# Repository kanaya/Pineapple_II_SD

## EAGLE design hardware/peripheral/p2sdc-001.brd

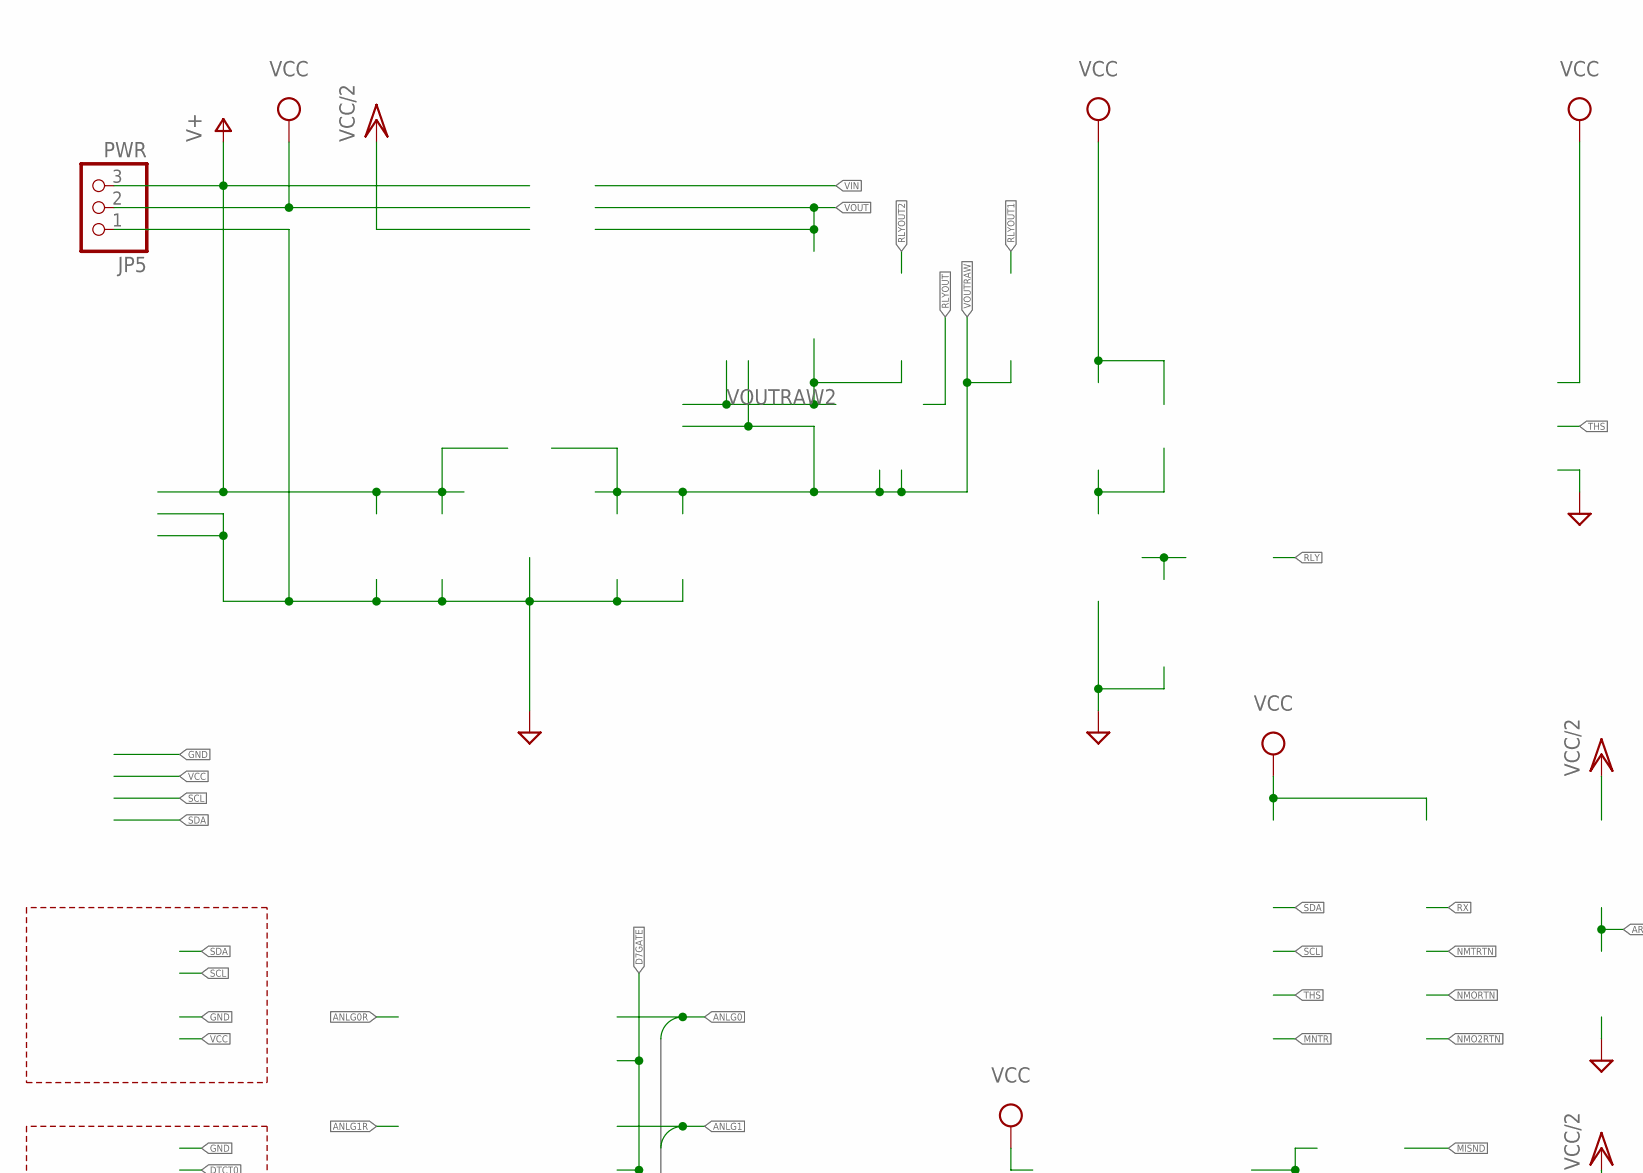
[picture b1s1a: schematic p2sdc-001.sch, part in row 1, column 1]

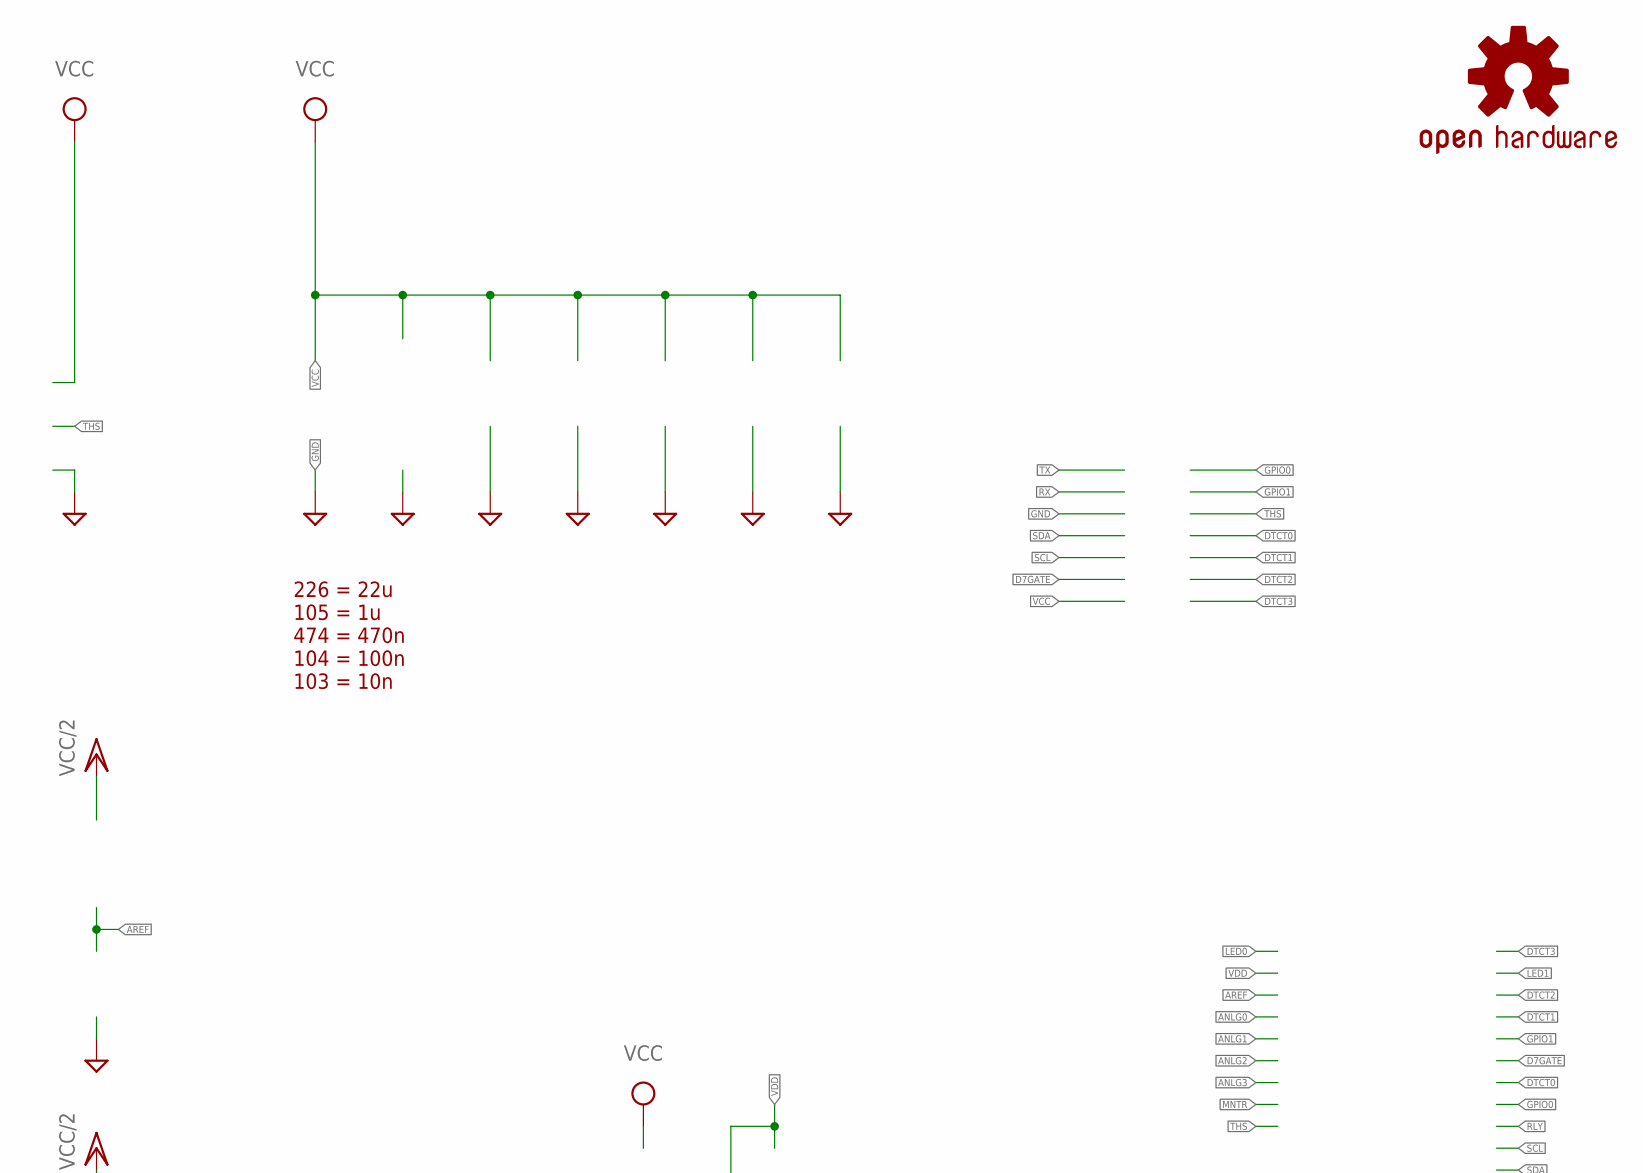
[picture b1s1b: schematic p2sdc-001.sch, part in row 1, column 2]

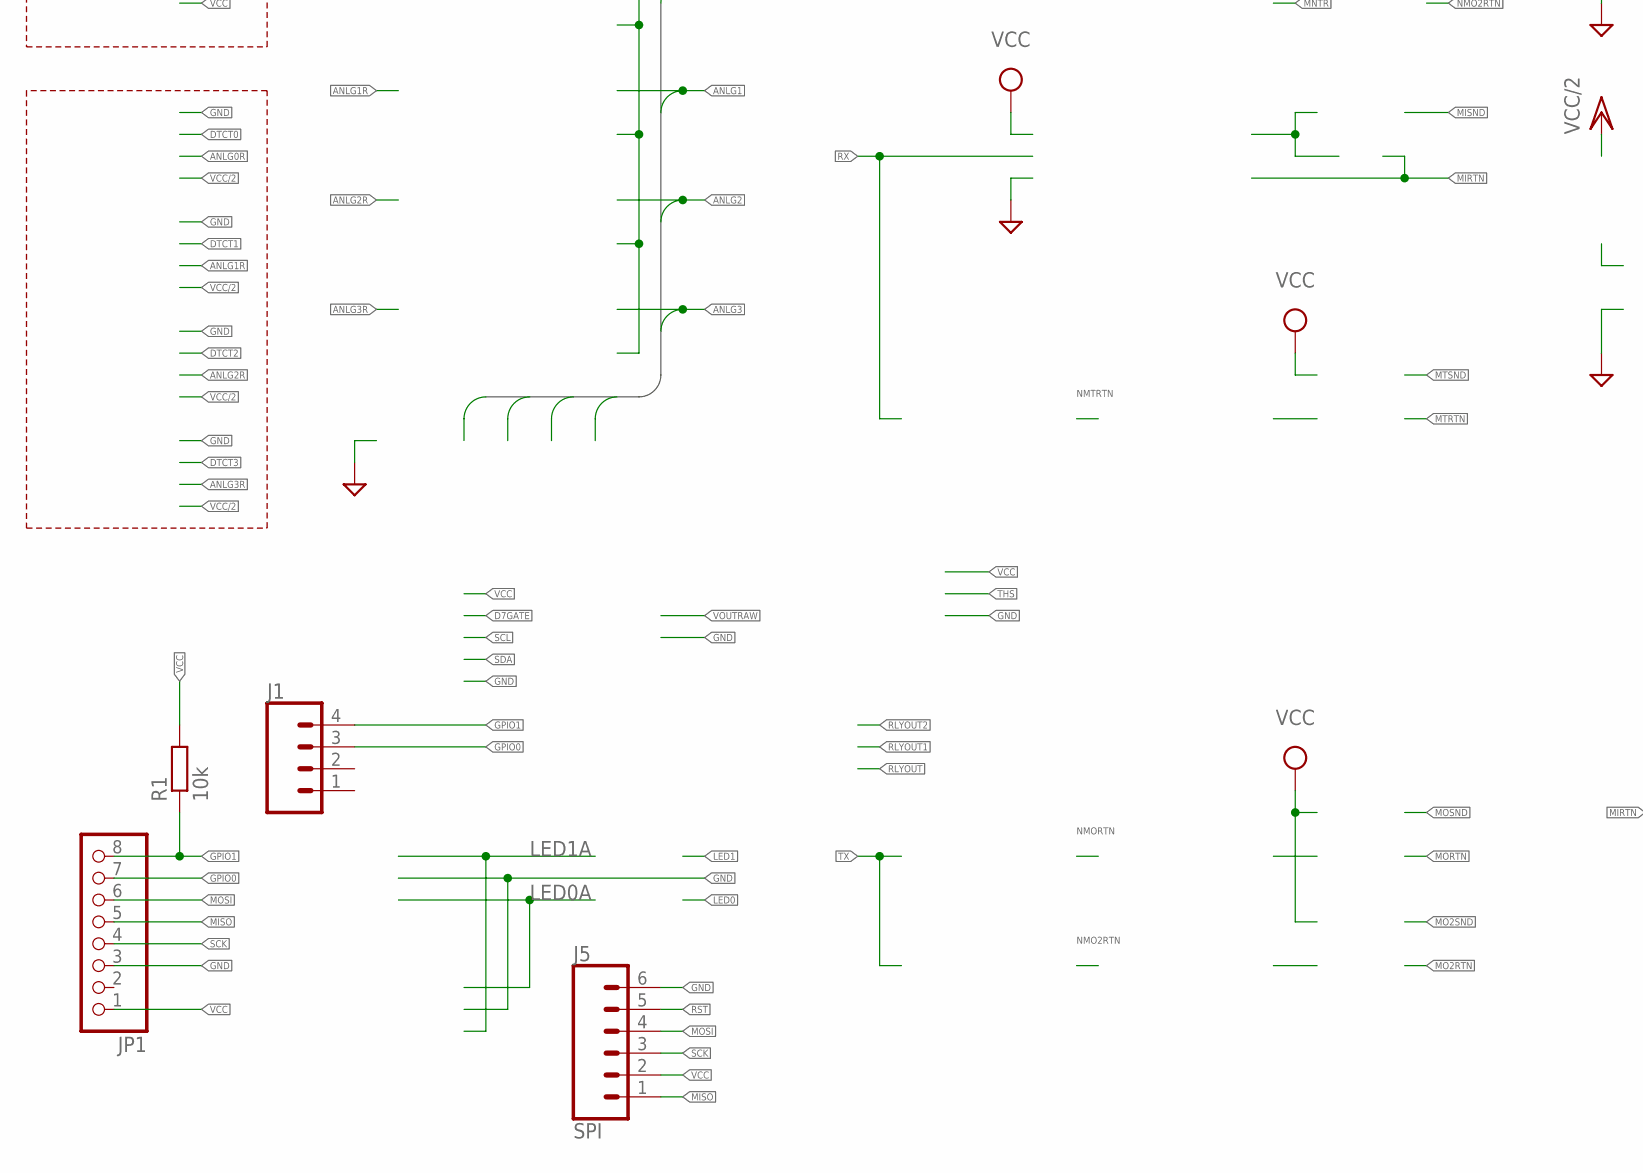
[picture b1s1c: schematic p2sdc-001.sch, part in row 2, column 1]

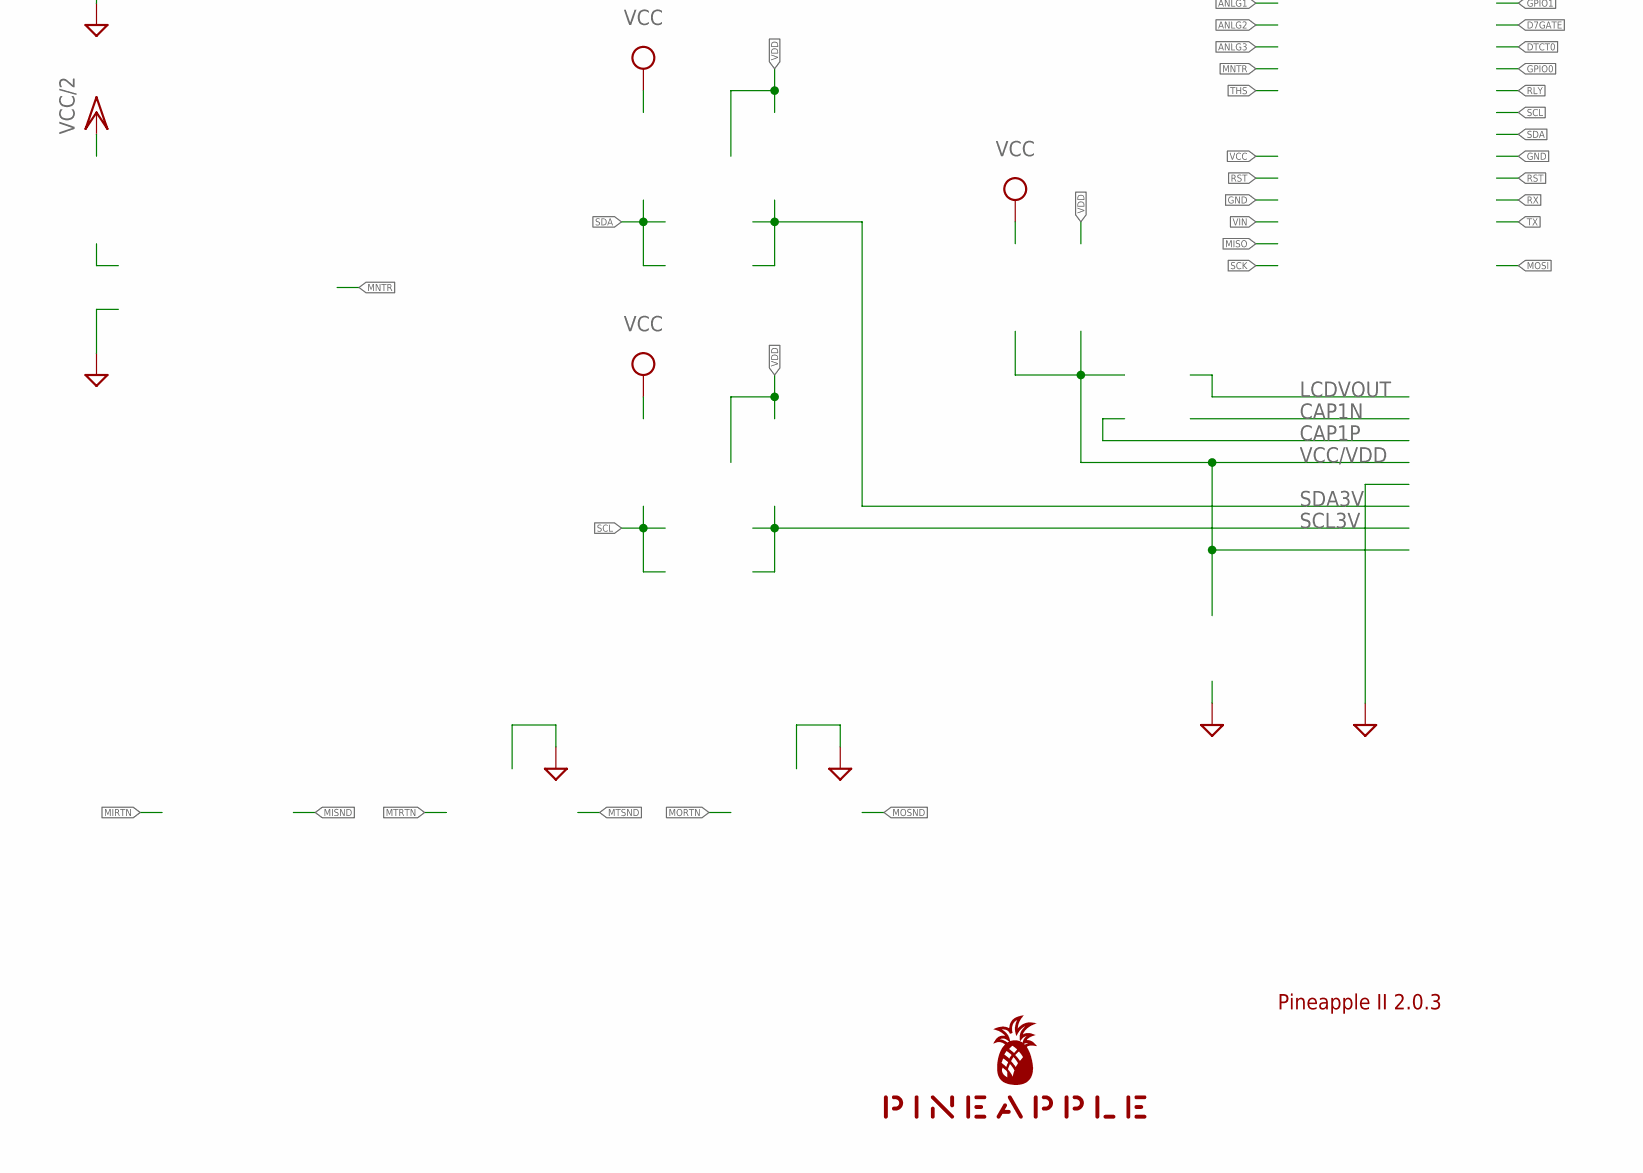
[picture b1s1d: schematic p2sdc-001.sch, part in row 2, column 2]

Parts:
J1: CONN_041.27MM; 1X04_1.27MM
J5: SPI; 1X06_1.27MM
JP1: PINHD-1X8; 1X08
JP5: PWR; 1X03
LOGO1: OSHW-LOGOS-COPPER; OSHW-LOGO-S_COPPER
R1: 10k; 0204/5
U$1: PINEAPPLE450_SILK

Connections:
GND: J5.6, JP1.3, JP5.1
GPIO0: J1.3, JP1.7
GPIO1: J1.4, JP1.8, R1.1
MISO: J5.1, JP1.5
MOSI: J5.4, JP1.6
RST: J5.5
SCK: J5.3, JP1.4
V+: JP5.3
VCC: J5.2, JP1.1, JP5.2, R1.2

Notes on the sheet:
Pineapple II 2.0.3
226 = 22u 105 = 1u 474 = 470n 104 = 100n 103 = 10n

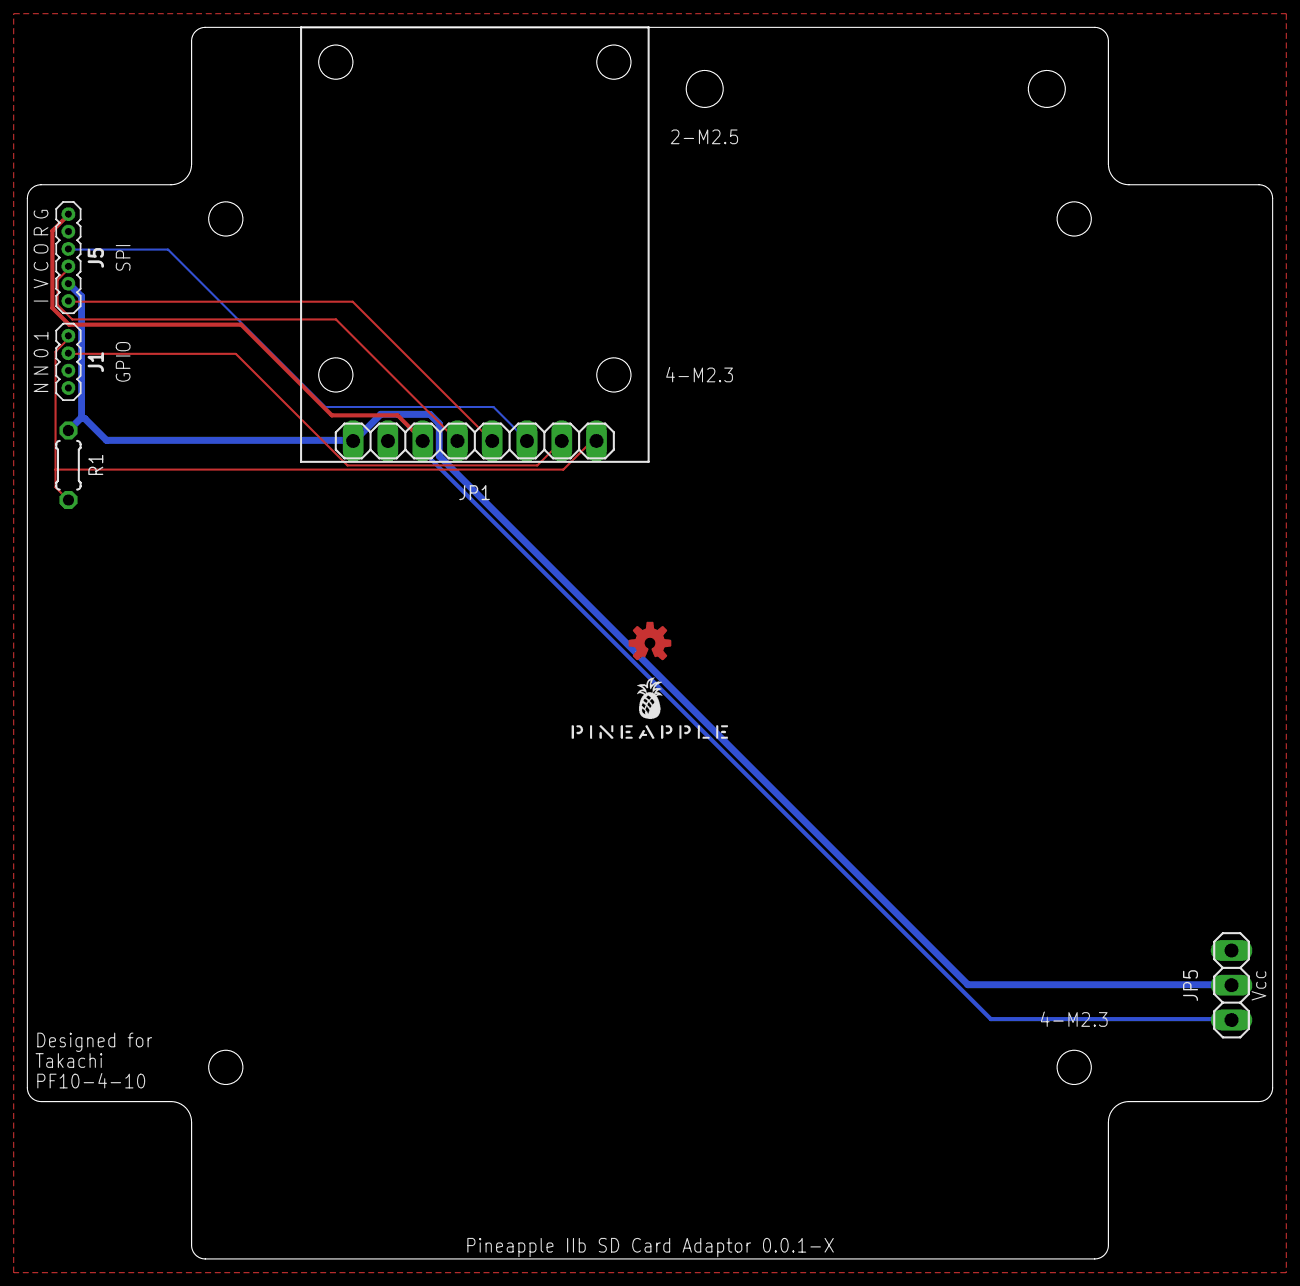
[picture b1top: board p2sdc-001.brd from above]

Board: 2 copper layers, 91.0 x 90.0 mm, 7 parts (0 on the bottom side), 7 nets.

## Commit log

2022-08-30 Initial import from Pineapple IIb 2.6.6.
2022-08-30 Removed parts.
2022-08-30 Positioning of the breakout card.
2022-08-30 First try.
2022-08-30 New interface.

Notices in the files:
parts and their libraries:
SparkFun-Aesthetics: Licensing: Creative Commons ShareAlike 4.0 International - https://creativecommons.org/licenses/by-sa/4.0
